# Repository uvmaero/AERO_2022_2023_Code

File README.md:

# AERO_2022-2023
All of the code that drives each board and runs the car for the year 2022-2023!

## Overview
Each board is managed by an ESP32-WROOM, in the form of the official Dev-Kit-C V4 from Espressif. Its operations are managed by FreeRTOS and is clocked at 240Mhz.

## Boards
### Front Board
#### Description
Located in the front of the car, this board manages all driver input, the remote data aquisition system, and wireless communications with the steering wheel.
#### I/O
##### Inputs
- Accelorator pedal
- Brake pedal 
- Ready to drive button
- front wheel hall effect sensors
- front wheel ride height potentiometers
- CAN bus
##### Outputs
- CAN bus
- LoRa Radio
- ESP NOW data to wheel board
- Ready to drive LED
- Ready to drive buzzer 
#### Libraries
- LoRa

### Rear Board
#### Description
#### I/O
#### Libraries

### Wheel Board
#### Description
#### I/O
#### Libraries

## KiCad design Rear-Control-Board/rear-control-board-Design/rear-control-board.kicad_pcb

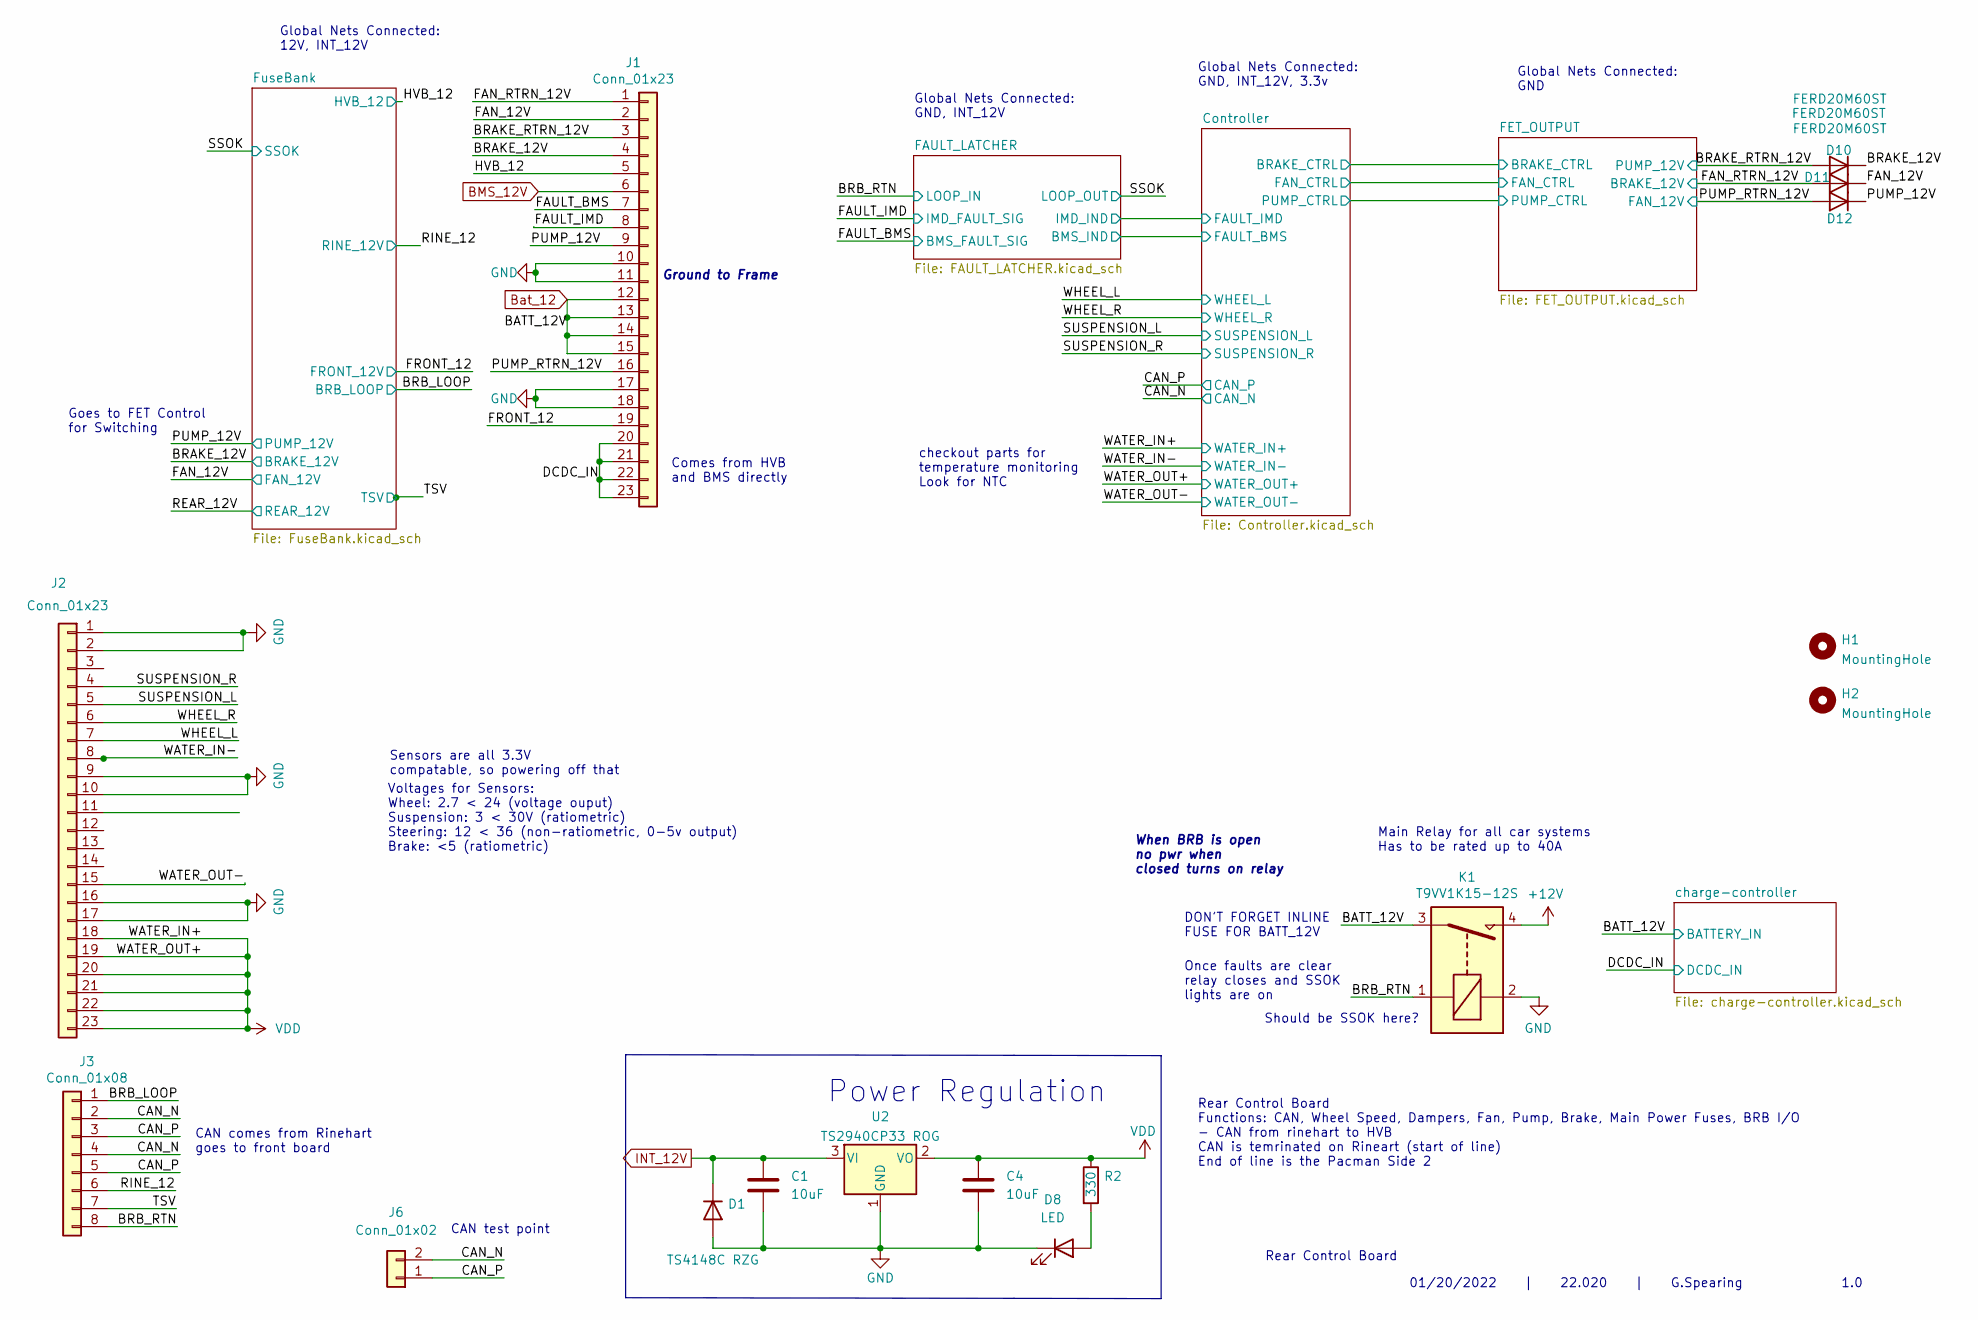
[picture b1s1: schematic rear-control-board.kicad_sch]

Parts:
C1, C4: 10uF; C_0603_1608Metric_Pad1.08x0.95mm_HandSolder
D1: TS4148C RZG; D_0603_1608Metric_Pad1.05x0.95mm_HandSolder
D8: LED; LED_0603_1608Metric_Pad1.05x0.95mm_HandSolder
D10, D11, D12: FERD20M60ST; TO-220-3_Vertical
H1, H2: MountingHole; MountingHole_3.2mm_M3
J1, J2: Conn_01x23; TE_1-770669-1_23pin_Horizontal
J3: Conn_01x08; TE_1-776280-1_8pin_Horizontal
J6: Conn_01x02; JST_NV_B02P-NV_1x02_P5.00mm_Vertical
K1: T9VV1K15-12S; RELAY_T9VV1K15-12S
R2: 330; R_0603_1608Metric_Pad0.98x0.95mm_HandSolder
U2: TS2940CP33 ROG; TO-252-2

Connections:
/BATT_12V: J1.12, J1.13, J1.14, J1.15, K1.3; also elsewhere on the board
/BRAKE_12V: D10.2 (K), J1.4; also elsewhere on the board
/BRAKE_RTRN_12V: D10.1 (A), J1.3; also elsewhere on the board
/BRB_LOOP: J3.1; also elsewhere on the board
/BRB_RTN: J3.8, K1.1; also elsewhere on the board
/CAN_N: J3.2, J3.4, J6.2; also elsewhere on the board
/CAN_P: J3.3, J3.5, J6.1; also elsewhere on the board
/DCDC_IN: J1.20, J1.21, J1.22, J1.23; also elsewhere on the board
/FAN_12V: D11.2 (K), J1.2; also elsewhere on the board
/FAN_RTRN_12V: D11.1 (A), J1.1; also elsewhere on the board
/FAULT_BMS: J1.7; also elsewhere on the board
/FAULT_IMD: J1.8; also elsewhere on the board
/FRONT_12: J1.19; also elsewhere on the board
/HVB_12: J1.5; also elsewhere on the board
/PUMP_12V: D12.2 (K), J1.9; also elsewhere on the board
/PUMP_RTRN_12V: D12.1 (A), J1.16; also elsewhere on the board
/RINE_12: J3.6; also elsewhere on the board
/SUSPENSION_L: J2.5; also elsewhere on the board
/SUSPENSION_R: J2.4; also elsewhere on the board
/TSV: J3.7; also elsewhere on the board
/WATER_IN-: J2.8; also elsewhere on the board
/WATER_OUT-: J2.15; also elsewhere on the board
/WHEEL_L: J2.7; also elsewhere on the board
/WHEEL_R: J2.6; also elsewhere on the board
BMS_12V: J1.6; also elsewhere on the board
GND: C1.2, C4.2, D1.2 (A), D8.1 (K), J1.10, J1.11, J1.17, J1.18, J2.1, J2.2, J2.9, J2.10, J2.16, J2.17, K1.2, U2.1 (GND); also elsewhere on the board
INT_12V: C1.1, D1.1 (K), U2.3 (VI); also elsewhere on the board
unnamed: D8.2 (A), R2.2
VDD: C4.1, J2.18, J2.19, J2.20, J2.21, J2.22, J2.23, R2.1, U2.2 (VO); also elsewhere on the board

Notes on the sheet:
Once faults are clear relay closes and SSOK lights are on
1.0
Comes from HVB and BMS directly
Should be SSOK here?
Global Nets Connected: GND
Main Relay for all car systems Has to be rated up to 40A
checkout parts for temperature monitoring Look for NTC
When BRB is open no pwr when closed turns on relay
Global Nets Connected: GND, INT_12V
Voltages for Sensors: Wheel: 2.7 < 24 (voltage ouput) Suspension: 3 < 30V (ratiometric) Steering: 12 < 36 (non-ratiometric, 0-5v output) Brake: <5 (ratiometric)
DON'T FORGET INLINE FUSE FOR BATT_12V
CAN test point
01/20/2022 | 22.020 | G.Spearing
Rear Control Board Functions: CAN, Wheel Speed, Dampers, Fan, Pump, Brake, Main Power Fuses, BRB I/O - CAN from rinehart to HVB CAN is temrinated on Rineart (start of line) End of line is the Pacman Side 2
Goes to FET Control for Switching
Ground to Frame
CAN comes from Rinehart goes to front board
Power Regulation
Global Nets Connected: GND, INT_12V, 3.3v
Sensors are all 3.3V compatable, so powering off that
Global Nets Connected: 12V, INT_12V
Rear Control Board

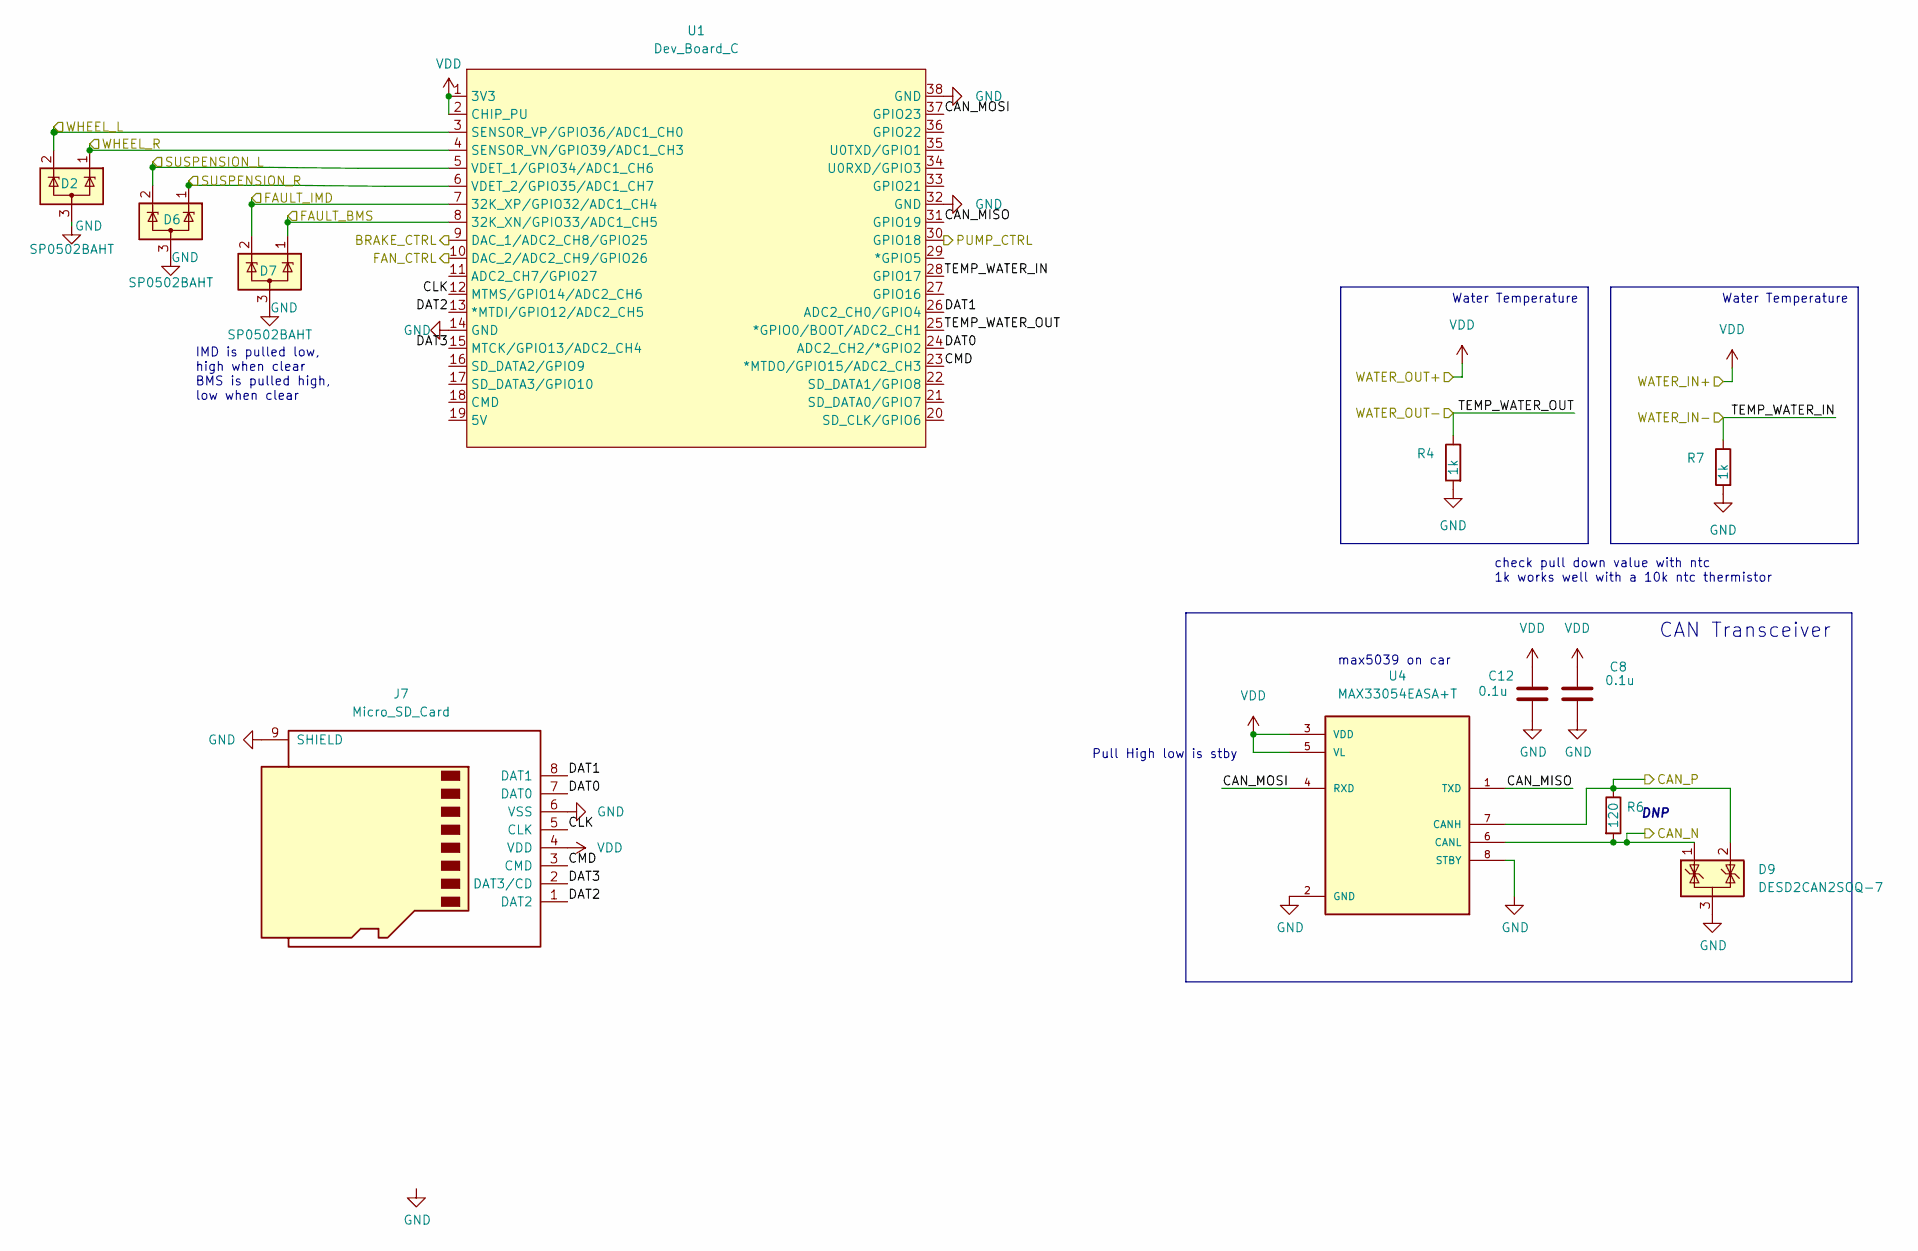
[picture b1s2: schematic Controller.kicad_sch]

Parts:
C8, C12: 0.1u; C_0603_1608Metric_Pad1.08x0.95mm_HandSolder
D2, D6, D7: SP0502BAHT; SOT-23
D9: DESD2CAN2SOQ-7; SOT-23
J7: Micro_SD_Card; microSD_HC_Wuerth_693072010801
R4, R7: 1k; R_0603_1608Metric_Pad0.98x0.95mm_HandSolder
R6: 120; R_0603_1608Metric_Pad0.98x0.95mm_HandSolder
U1: Dev_Board_C; ESP32-DevKitC
U4: MAX33054EASA+T; SOIC127P600X175-8N

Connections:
/CAN_N: D9.1 (K), R6.2, U4.6 (CANL); also elsewhere on the board
/CAN_P: D9.2 (K), R6.1, U4.7 (CANH); also elsewhere on the board
/Controller/BRAKE_CTRL: U1.9 (DAC_1/ADC2_CH8/GPIO25); also elsewhere on the board
/Controller/CAN_MISO: U1.31 (GPIO19), U4.1 (TXD)
/Controller/CAN_MOSI: U1.37 (GPIO23), U4.4 (RXD)
/Controller/CLK: J7.5 (CLK), U1.12 (MTMS/GPIO14/ADC2_CH6)
/Controller/CMD: J7.3 (CMD), U1.23 (*MTDO/GPIO15/ADC2_CH3)
/Controller/DAT0: J7.7 (DAT0), U1.24 (ADC2_CH2/*GPIO2)
/Controller/DAT1: J7.8 (DAT1), U1.26 (ADC2_CH0/GPIO4)
/Controller/DAT2: J7.1 (DAT2), U1.13 (*MTDI/GPIO12/ADC2_CH5)
/Controller/DAT3: J7.2 (DAT3/CD), U1.15 (MTCK/GPIO13/ADC2_CH4)
/Controller/FAN_CTRL: U1.10 (DAC_2/ADC2_CH9/GPIO26); also elsewhere on the board
/Controller/FAULT_IMD: D7.2 (K), U1.7 (32K_XP/GPIO32/ADC1_CH4); also elsewhere on the board
/Controller/PUMP_CTRL: U1.30 (GPIO18); also elsewhere on the board
/FAULT_LATCHER/BMS_SWITCH: D7.1 (K), U1.8 (32K_XN/GPIO33/ADC1_CH5); also elsewhere on the board
/SUSPENSION_L: D6.2 (K), U1.5 (VDET_1/GPIO34/ADC1_CH6); also elsewhere on the board
/SUSPENSION_R: D6.1 (K), U1.6 (VDET_2/GPIO35/ADC1_CH7); also elsewhere on the board
/WATER_IN-: R7.1, U1.28 (GPIO17); also elsewhere on the board
/WATER_OUT-: R4.1, U1.25 (*GPIO0/BOOT/ADC2_CH1); also elsewhere on the board
/WHEEL_L: D2.2 (K), U1.3 (SENSOR_VP/GPIO36/ADC1_CH0); also elsewhere on the board
/WHEEL_R: D2.1 (K), U1.4 (SENSOR_VN/GPIO39/ADC1_CH3); also elsewhere on the board
GND: C8.2, C12.2, D2.3 (A), D6.3 (A), D7.3 (A), D9.3 (A), J7.6 (VSS), J7.9 (SHIELD), R4.2, R7.2, U1.14 (GND), U1.32 (GND), U1.38 (GND), U4.2 (GND), U4.8 (STBY); also elsewhere on the board
VDD: C8.1, C12.1, J7.4 (VDD), U1.1 (3V3), U1.2 (CHIP_PU), U4.3 (VDD), U4.5 (VL); also elsewhere on the board

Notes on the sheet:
Water Temperature
check pull down value with ntc 1k works well with a 10k ntc thermistor
CAN Transceiver
IMD is pulled low, high when clear BMS is pulled high, low when clear
max5039 on car
Pull High low is stby
DNP

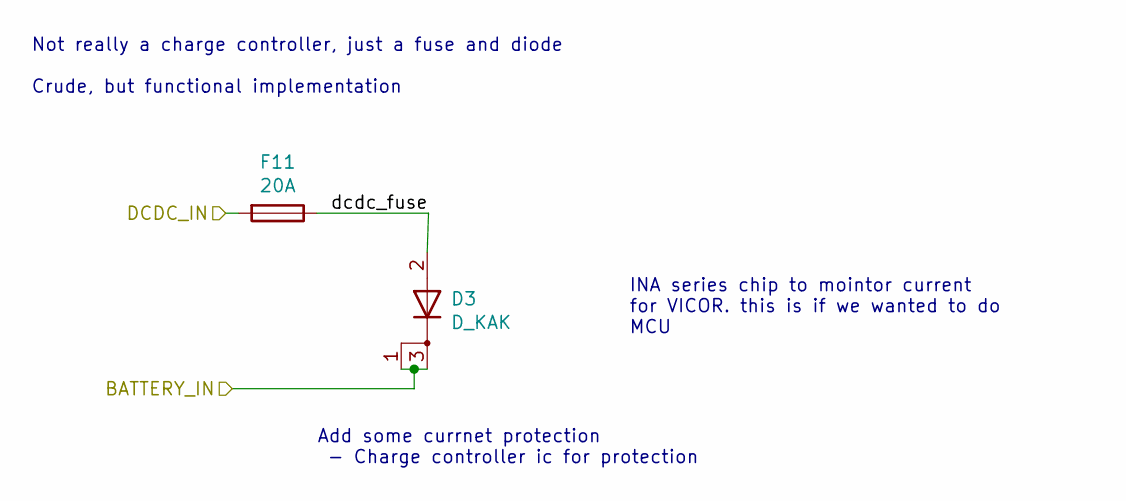
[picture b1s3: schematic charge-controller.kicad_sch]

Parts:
D3: D_KAK; TO-252-2
F11: 20A; Fuseholder_Blade_Mini_Keystone_3568

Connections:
/BATT_12V: D3.1 (K), D3.3 (K); also elsewhere on the board
/DCDC_IN: F11.2; also elsewhere on the board
/charge-controller/dcdc_fuse: D3.2 (A), F11.1

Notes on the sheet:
Add some currnet protection - Charge controller ic for protection
Not really a charge controller, just a fuse and diode Crude, but functional implementation
INA series chip to mointor current for VICOR. this is if we wanted to do MCU

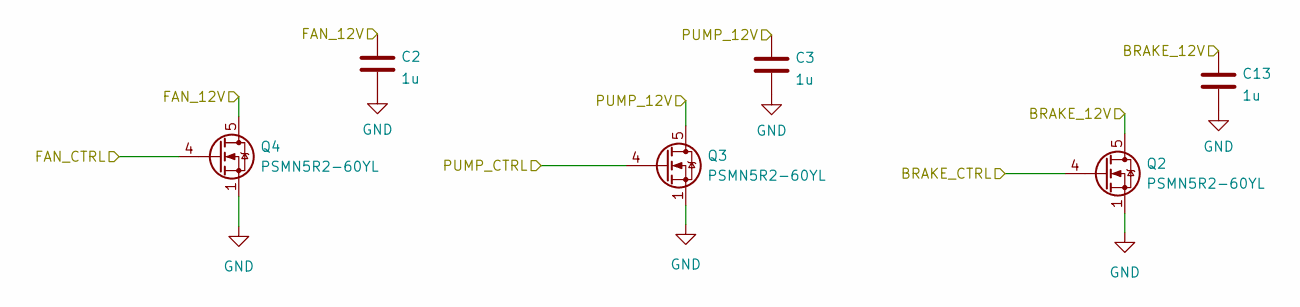
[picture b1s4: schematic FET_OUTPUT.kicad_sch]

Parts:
C2, C3, C13: 1u; C_0603_1608Metric_Pad1.08x0.95mm_HandSolder
Q2, Q3, Q4: PSMN5R2-60YL; LFPAK56

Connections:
/BRAKE_RTRN_12V: C3.1, Q3.5 (D); also elsewhere on the board
/Controller/BRAKE_CTRL: Q2.4 (G); also elsewhere on the board
/Controller/FAN_CTRL: Q4.4 (G); also elsewhere on the board
/Controller/PUMP_CTRL: Q3.4 (G); also elsewhere on the board
/FAN_RTRN_12V: C13.1, Q2.5 (D); also elsewhere on the board
/PUMP_RTRN_12V: C2.1, Q4.5 (D); also elsewhere on the board
GND: C2.2, C3.2, C13.2, Q2.1 (S), Q2.2 (S), Q2.3 (S), Q3.1 (S), Q3.2 (S), Q3.3 (S), Q4.1 (S), Q4.2 (S), Q4.3 (S); also elsewhere on the board

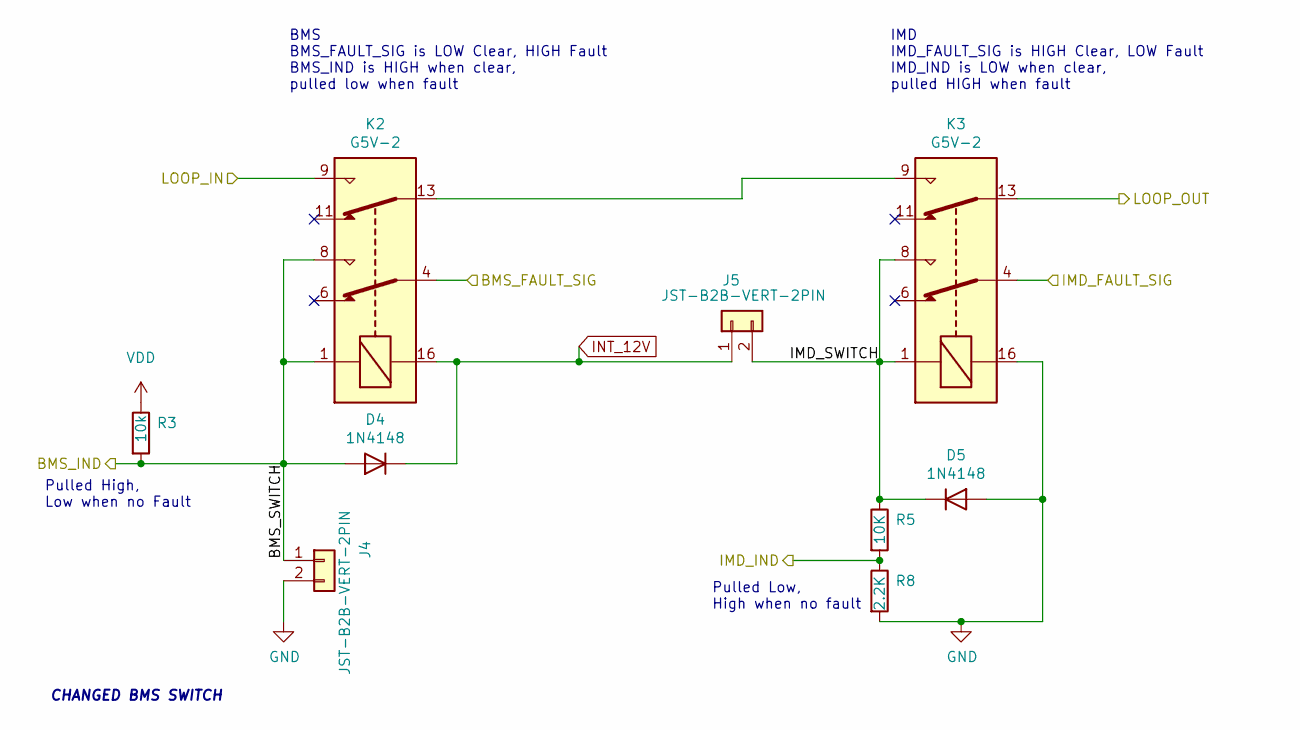
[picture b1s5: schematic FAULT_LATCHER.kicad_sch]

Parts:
D4, D5: 1N4148; D_SOD-123
J4, J5: JST-B2B-VERT-2PIN; JST_XH_B2B-XH-AM_1x02_P2.50mm_Vertical
K2, K3: G5V-2; Relay_DPDT_Omron_G5V-2
R3: 10k; R_0603_1608Metric_Pad0.98x0.95mm_HandSolder
R5: 10K; R_0603_1608Metric_Pad0.98x0.95mm_HandSolder
R8: 2.2K; R_0603_1608Metric_Pad0.98x0.95mm_HandSolder

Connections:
/BRB_RTN: K2.9; also elsewhere on the board
/Controller/FAULT_IMD: R5.2, R8.1; also elsewhere on the board
/FAULT_BMS: K2.4; also elsewhere on the board
/FAULT_IMD: K3.4; also elsewhere on the board
/FAULT_LATCHER/BMS_SWITCH: D4.2 (A), J4.1, K2.1, K2.8, R3.2; also elsewhere on the board
/FAULT_LATCHER/IMD_SWITCH: D5.1 (K), J5.2, K3.1, K3.8, R5.1
/SSOK: K3.13; also elsewhere on the board
GND: D5.2 (A), J4.2, K3.16, R8.2; also elsewhere on the board
INT_12V: D4.1 (K), J5.1, K2.16; also elsewhere on the board
unnamed: K2.13, K3.9
VDD: R3.1; also elsewhere on the board

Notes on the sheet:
Pulled High, Low when no Fault
IMD IMD_FAULT_SIG is HIGH Clear, LOW Fault IMD_IND is LOW when clear, pulled HIGH when fault
Pulled Low, High when no fault
BMS BMS_FAULT_SIG is LOW Clear, HIGH Fault BMS_IND is HIGH when clear, pulled low when fault
CHANGED BMS SWITCH

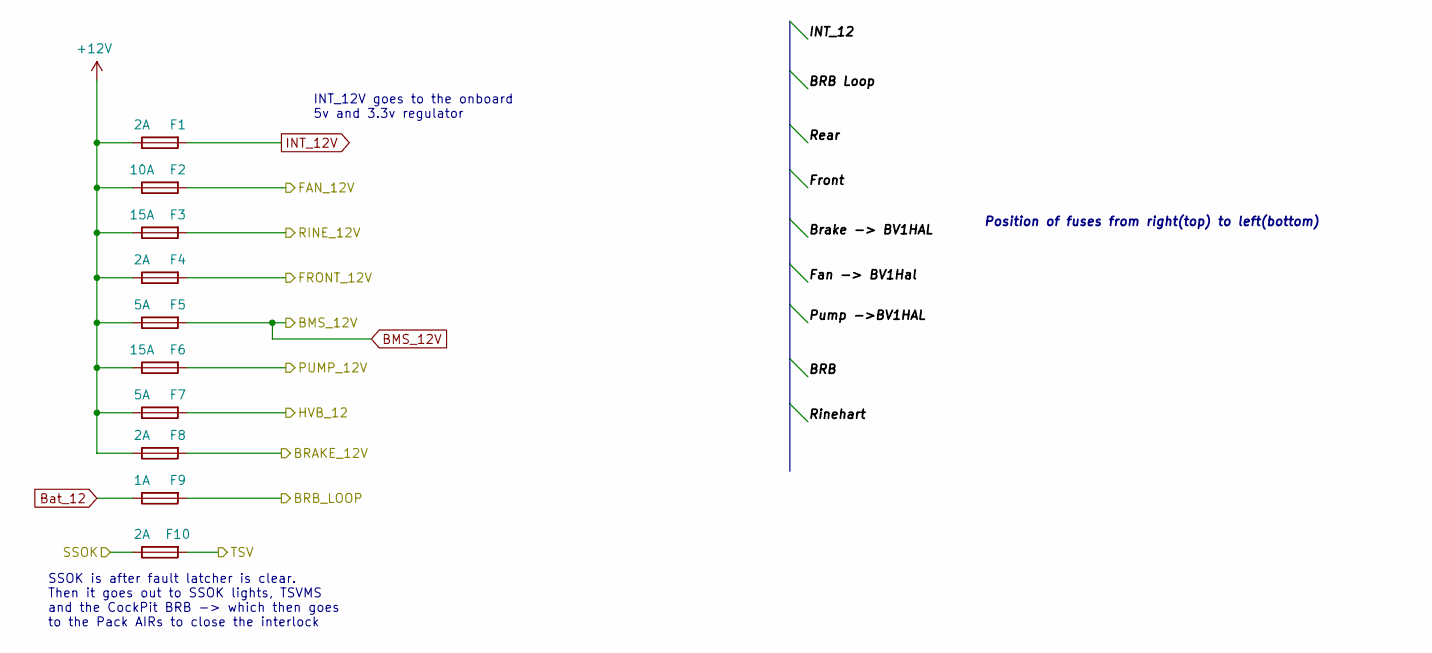
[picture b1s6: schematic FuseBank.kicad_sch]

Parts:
F1, F4, F8, F10: 2A; Fuseholder_Blade_Mini_Keystone_3568
F2: 10A; Fuseholder_Blade_Mini_Keystone_3568
F3, F6: 15A; Fuseholder_Blade_Mini_Keystone_3568
F5, F7: 5A; Fuseholder_Blade_Mini_Keystone_3568
F9: 1A; Fuseholder_Blade_Mini_Keystone_3568

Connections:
/BRAKE_12V: F8.2; also elsewhere on the board
/BRB_LOOP: F9.2; also elsewhere on the board
/FAN_12V: F2.2; also elsewhere on the board
/FRONT_12: F4.2; also elsewhere on the board
/HVB_12: F7.2; also elsewhere on the board
/PUMP_12V: F6.2; also elsewhere on the board
/RINE_12: F3.2; also elsewhere on the board
/SSOK: F10.1; also elsewhere on the board
/TSV: F10.2; also elsewhere on the board
BMS_12V: F5.2; also elsewhere on the board
INT_12V: F1.2; also elsewhere on the board

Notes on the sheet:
SSOK is after fault latcher is clear. Then it goes out to SSOK lights, TSVMS and the CockPit BRB -> which then goes to the Pack AIRs to close the interlock
Position of fuses from right(top) to left(bottom)
INT_12V goes to the onboard 5v and 3.3v regulator

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
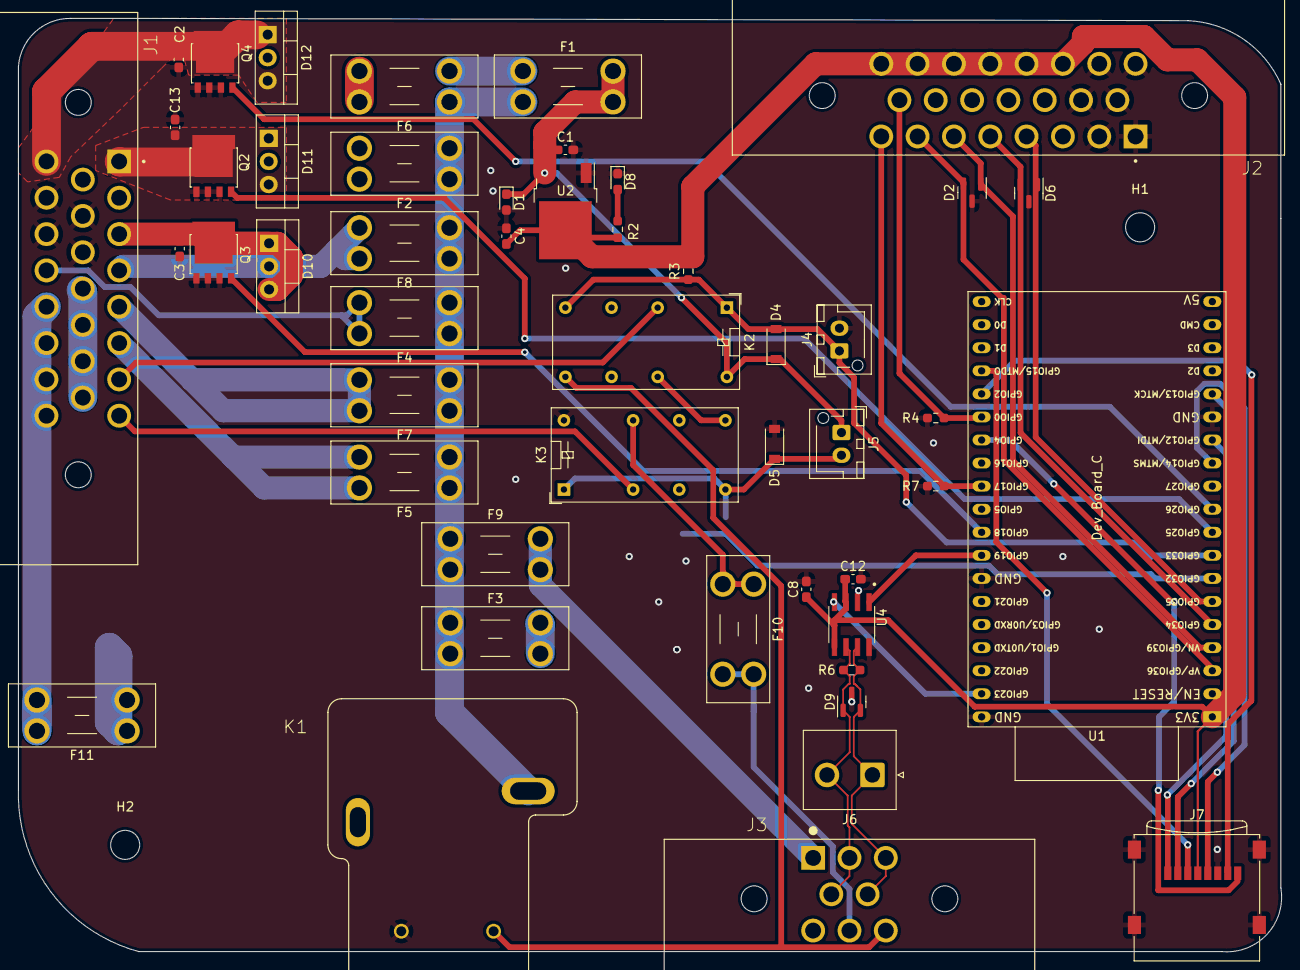
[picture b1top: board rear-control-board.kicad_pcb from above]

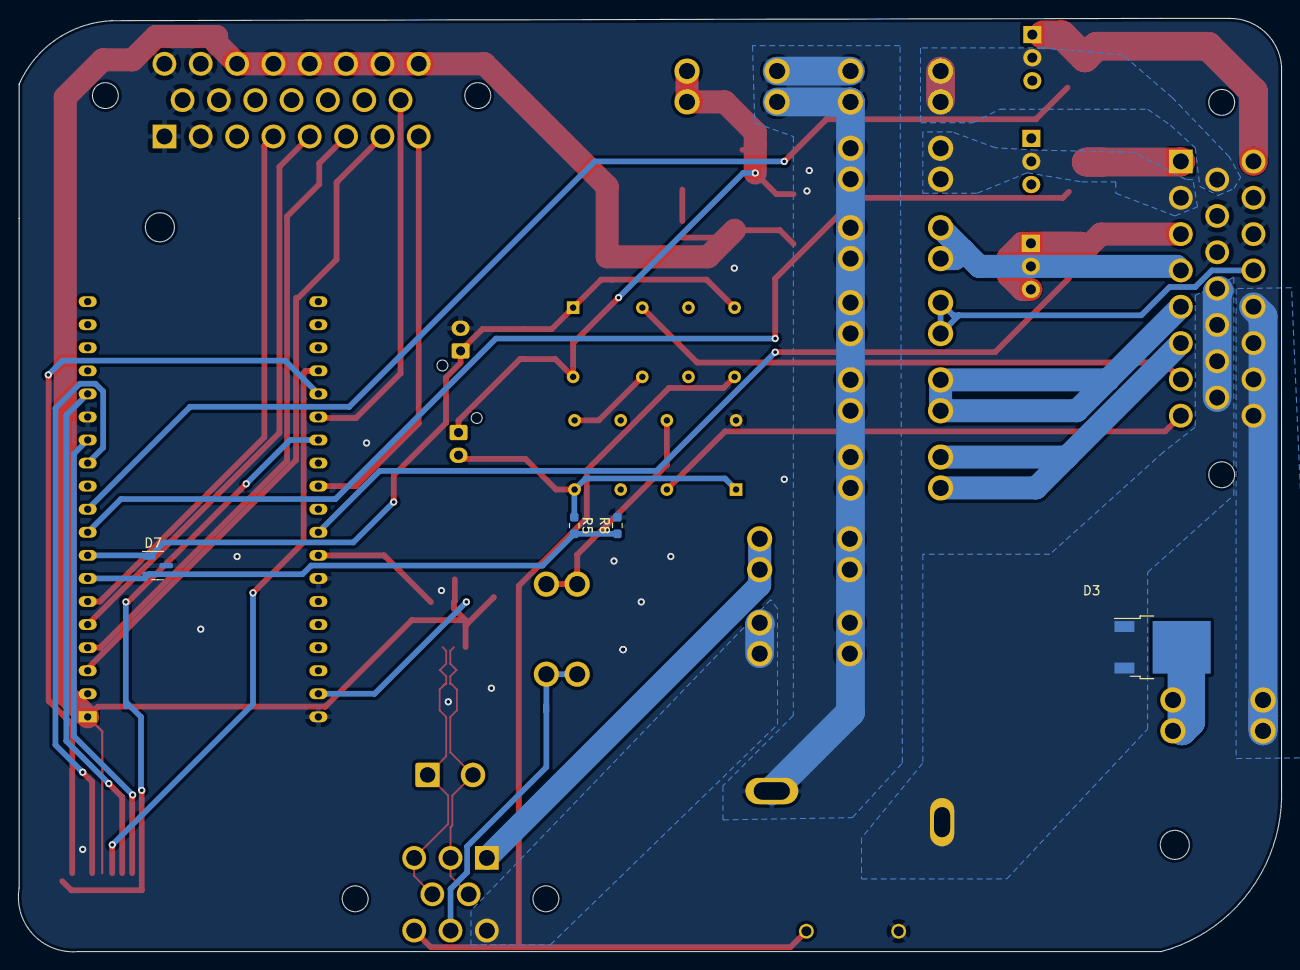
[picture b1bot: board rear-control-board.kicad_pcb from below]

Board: 2 copper layers, 139.1 x 102.8 mm, 55 parts (4 on the bottom side), 47 nets.

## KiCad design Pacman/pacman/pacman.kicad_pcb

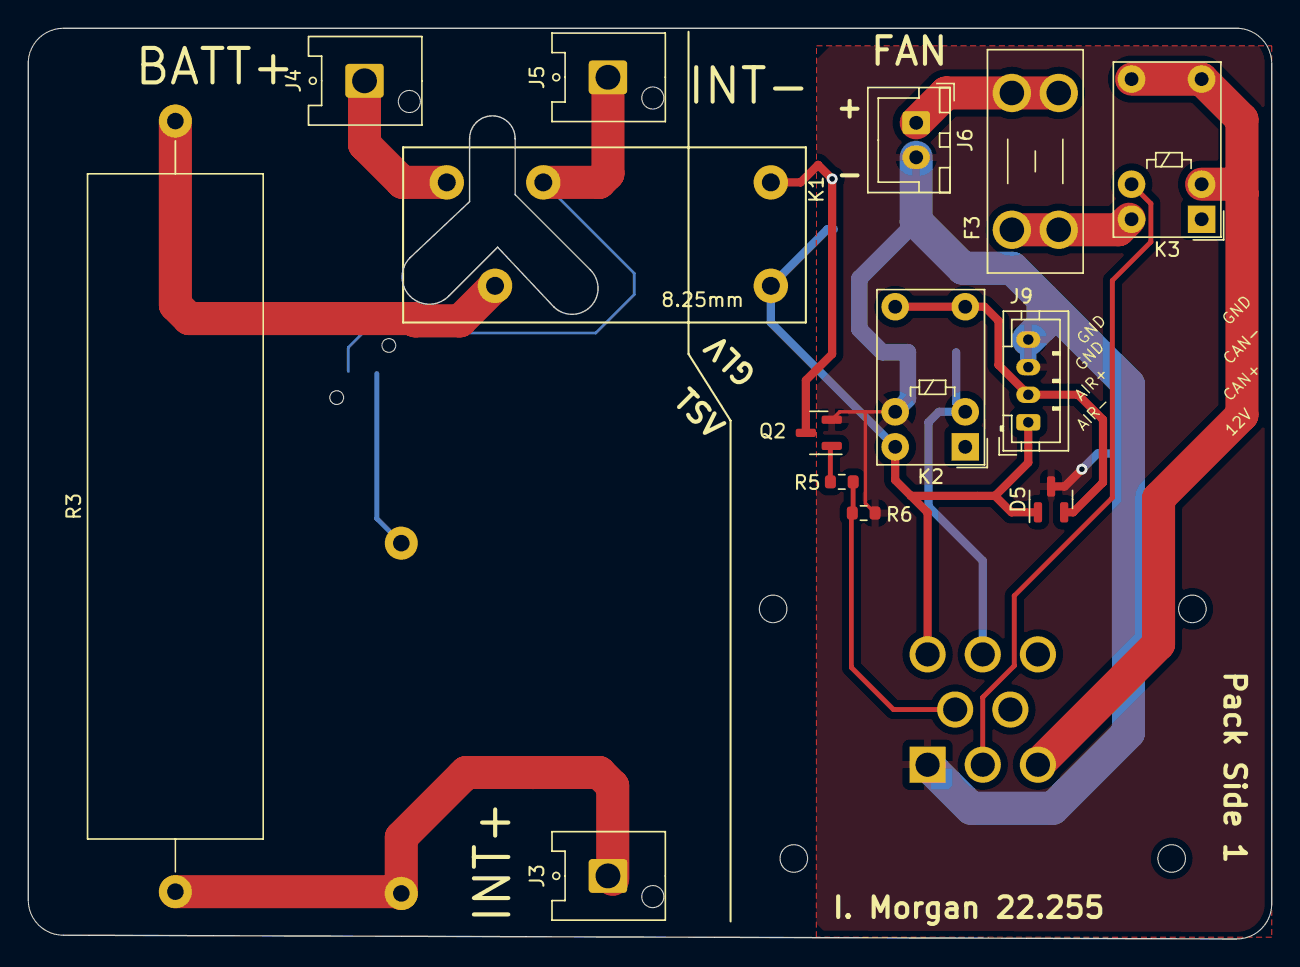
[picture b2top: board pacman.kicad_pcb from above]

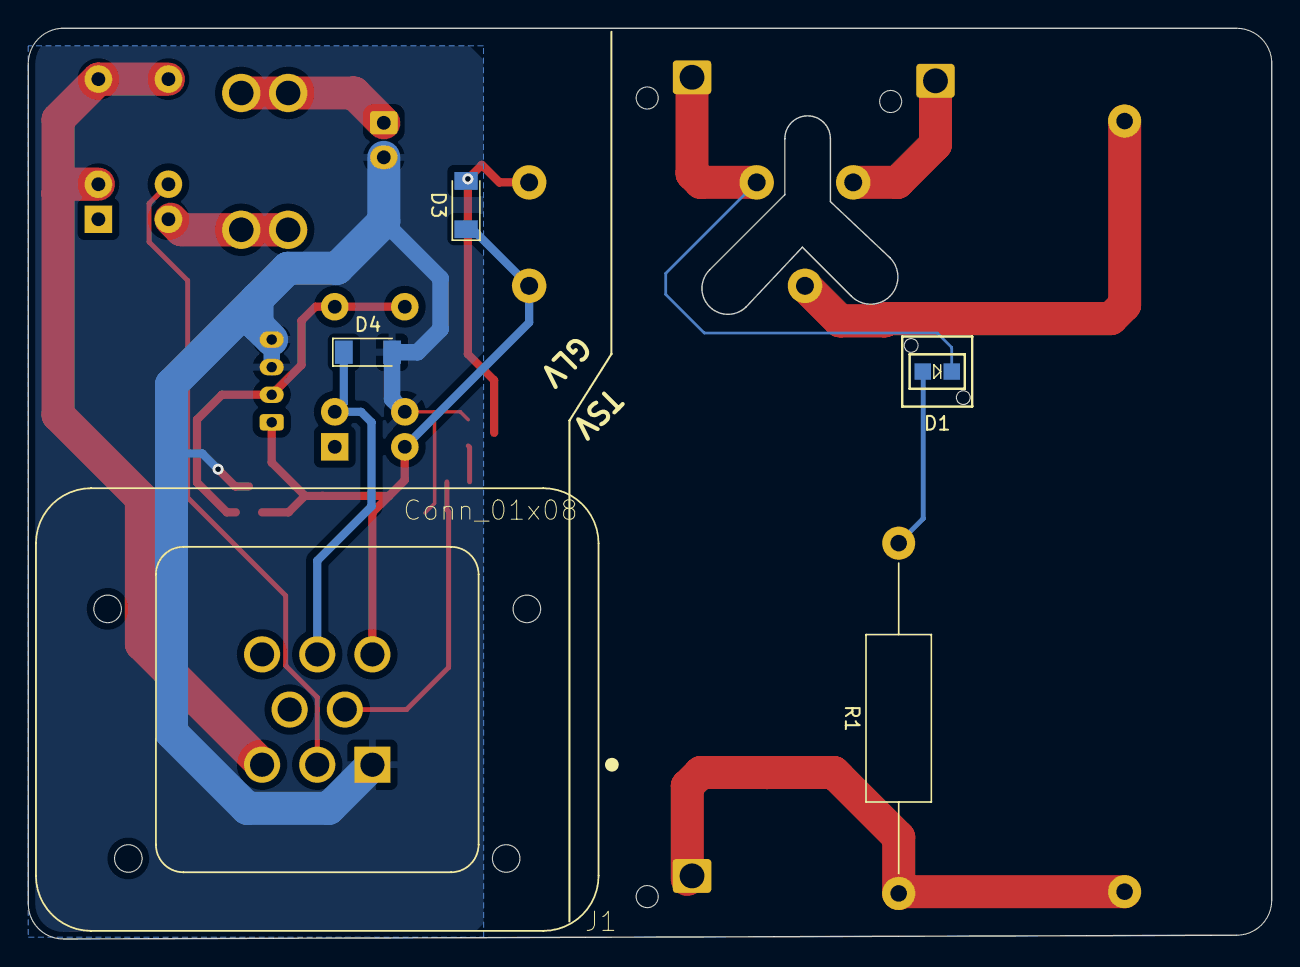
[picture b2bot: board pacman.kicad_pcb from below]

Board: 2 copper layers, 90.2 x 66.0 mm, 19 parts (5 on the bottom side), 16 nets.

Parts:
D1: LED; LPA-C011301S-x LED 0805 LIGHT PIPE SINGLE VERT SMD
D3, D4: 1N4148; D_MiniMELF
D5: MMBZxx; SOT-23
F3: Fuse; Fuseholder_Blade_Mini_Keystone_3568
J1: Conn_01x08; TE_1-776276-1_8pin_Vertical
J3, J4, J5: Conn_01x01; Hirose_DF63M-1P-3.96DSA_1x01_P3.96mm_Vertical
J6: Conn_01x02; JST_XH_B2B-XH-A_1x02_P2.50mm_Vertical
J9: JST PH; JST_PH_B4B-PH-K_1x04_P2.00mm_Vertical
K1: G2RL
K2, K3: G5V-1; Relay_SPDT_Omron_G5V-1
Q2: MMBT2222A; SOT-23
R1: 1.5k; R_Axial_DIN0414_L11.9mm_D4.5mm_P25.40mm_Horizontal
R3: 500; R_Axial_Power_L48.0mm_W12.5mm_P55.88mm
R5: 10k; R_0603_1608Metric
R6: 2k; R_0603_1608Metric

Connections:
+12V: J1.3, K3.2, K3.5, K3.6
/AIR_B+: D5.2 (K), J9.2, K2.5, K2.6
/AIR_B-: D3.1 (K), D5.1 (K), J1.6, J9.1, K1.2, K2.10
/B+: J4.1, K1.10
/BMS_FAN: J1.2, K3.9
/FAN_OUT: F3.1, K3.10
/INT+: J3.1, R1.1, R3.1
/INT-: D1.1 (K), J5.1, K1.1
/MAIN_CONT: D4.1 (K), J1.7, K2.2
/PRECHARGE: J1.4, R5.2, R6.2
GND: D4.2 (A), D5.3 (A), J1.1, J6.2, J9.3, J9.4, K2.9, Q2.2 (E), R6.1
unnamed: D1.2 (A), R1.2
unnamed: D3.2 (A), K1.9, Q2.3 (C)
unnamed: F3.2, J6.1
unnamed: K1.5, R3.2
unnamed: Q2.1 (B), R5.1

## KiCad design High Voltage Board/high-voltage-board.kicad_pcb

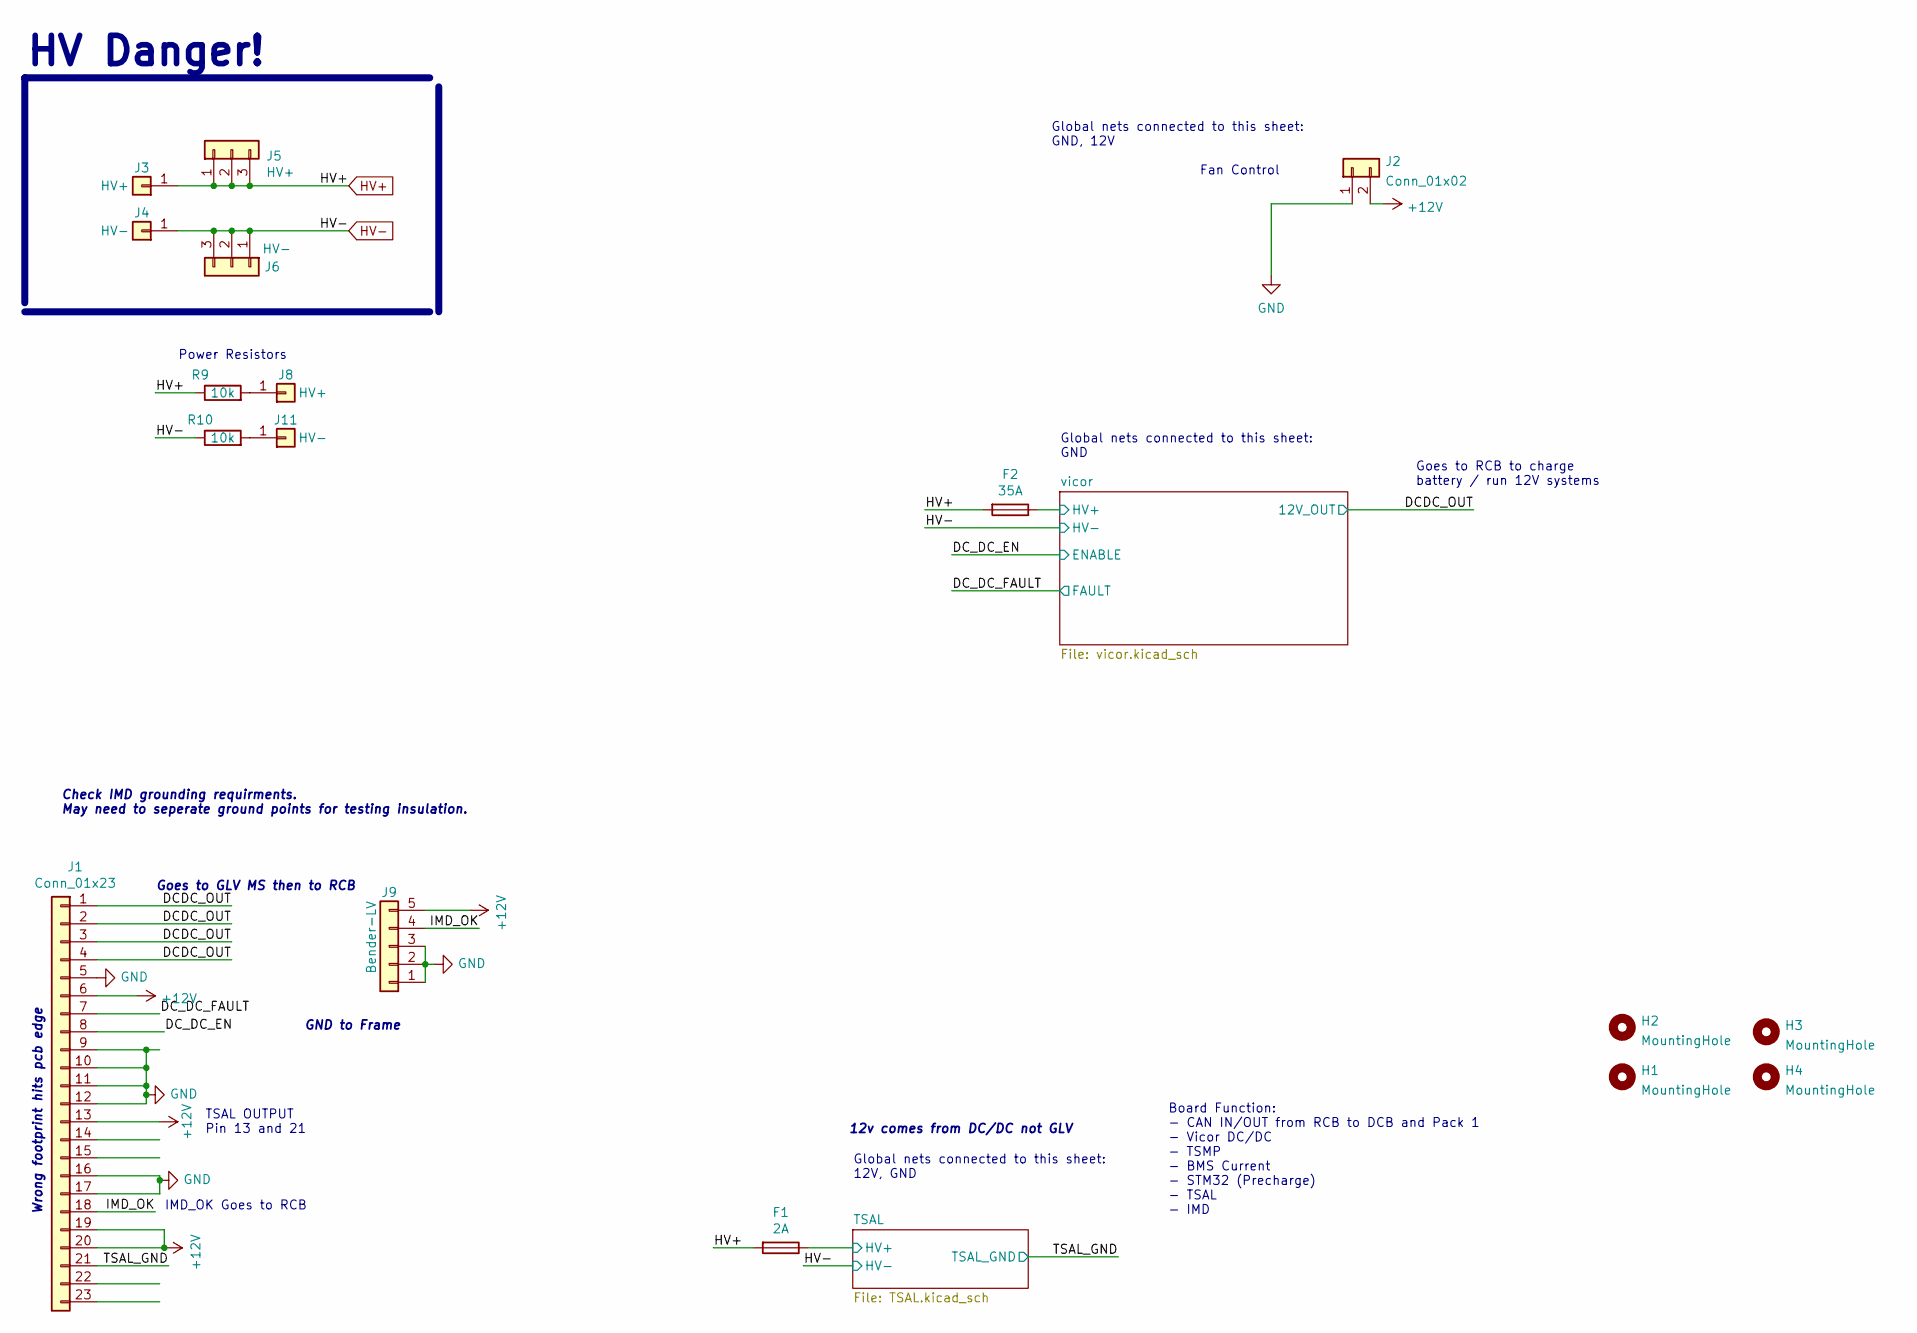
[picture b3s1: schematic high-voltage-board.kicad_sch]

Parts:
F1: 2A; Fuseholder_Cylinder-5x20mm_Schurter_0031_8201_Horizontal_Op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
F2: 35A; Fuseholder_Cylinder-5x20mm_Schurter_0031_8201_Horizontal_Op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
H1, H2, H3, H4: MountingHole; MountingHole_3.2mm_M3
J1: Conn_01x23; TE_1-770669-1_23pin_Horizontal
J2: Conn_01x02; JST_XH_B2B-XH-A_1x02_P2.50mm_Vertical
J3, J8: HV+; Hirose_DF63M-1P-3.96DSA_1x01_P3.96mm_Vertical
J4, J11: HV-; Hirose_DF63M-1P-3.96DSA_1x01_P3.96mm_Vertical
J5: HV+; TE_MATE-N-LOK_1-770870-x_1x03_P4.14mm_Vertical
J6: HV-; TE_MATE-N-LOK_1-770870-x_1x03_P4.14mm_Vertical
J9: Bender-LV; JST_XH_B5B-XH-A_1x05_P2.50mm_Vertical
R9, R10: 10k; R_Axial_Power_L50.0mm_W9.0mm_P60.96mm

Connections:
+12V: J1.6, J1.13, J1.19, J1.20, J2.2, J9.5; also elsewhere on the board
/DCDC_OUT: J1.1, J1.2, J1.3, J1.4; also elsewhere on the board
/DC_DC_EN: J1.8; also elsewhere on the board
/DC_DC_FAULT: J1.7; also elsewhere on the board
/IMD_OK: J1.18, J9.4
/TSAL/HV+: F1.1; also elsewhere on the board
/TSAL_GND: J1.21; also elsewhere on the board
/vicor/HV+: F2.1; also elsewhere on the board
GND: J1.5, J1.9, J1.10, J1.11, J1.12, J1.16, J1.17, J2.1, J9.1, J9.2, J9.3; also elsewhere on the board
HV+: F1.2, F2.2, J3.1, J5.1, J5.2, J5.3, R9.1
HV-: J4.1, J6.1, J6.2, J6.3, R10.1; also elsewhere on the board
unnamed: J8.1, R9.2
unnamed: J11.1, R10.2

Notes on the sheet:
Global nets connected to this sheet: GND, 12V
Global nets connected to this sheet: 12V, GND
IMD_OK Goes to RCB
Goes to RCB to charge battery / run 12V systems
TSAL OUTPUT Pin 13 and 21
Board Function: - CAN IN/OUT from RCB to DCB and Pack 1 - Vicor DC/DC - TSMP - BMS Current - STM32 (Precharge) - TSAL - IMD
Power Resistors
12v comes from DC/DC not GLV
Goes to GLV MS then to RCB
Fan Control
GND to Frame
Global nets connected to this sheet: GND
HV Danger!
Check IMD grounding requirments. May need to seperate ground points for testing insulation.
Wrong footprint hits pcb edge
